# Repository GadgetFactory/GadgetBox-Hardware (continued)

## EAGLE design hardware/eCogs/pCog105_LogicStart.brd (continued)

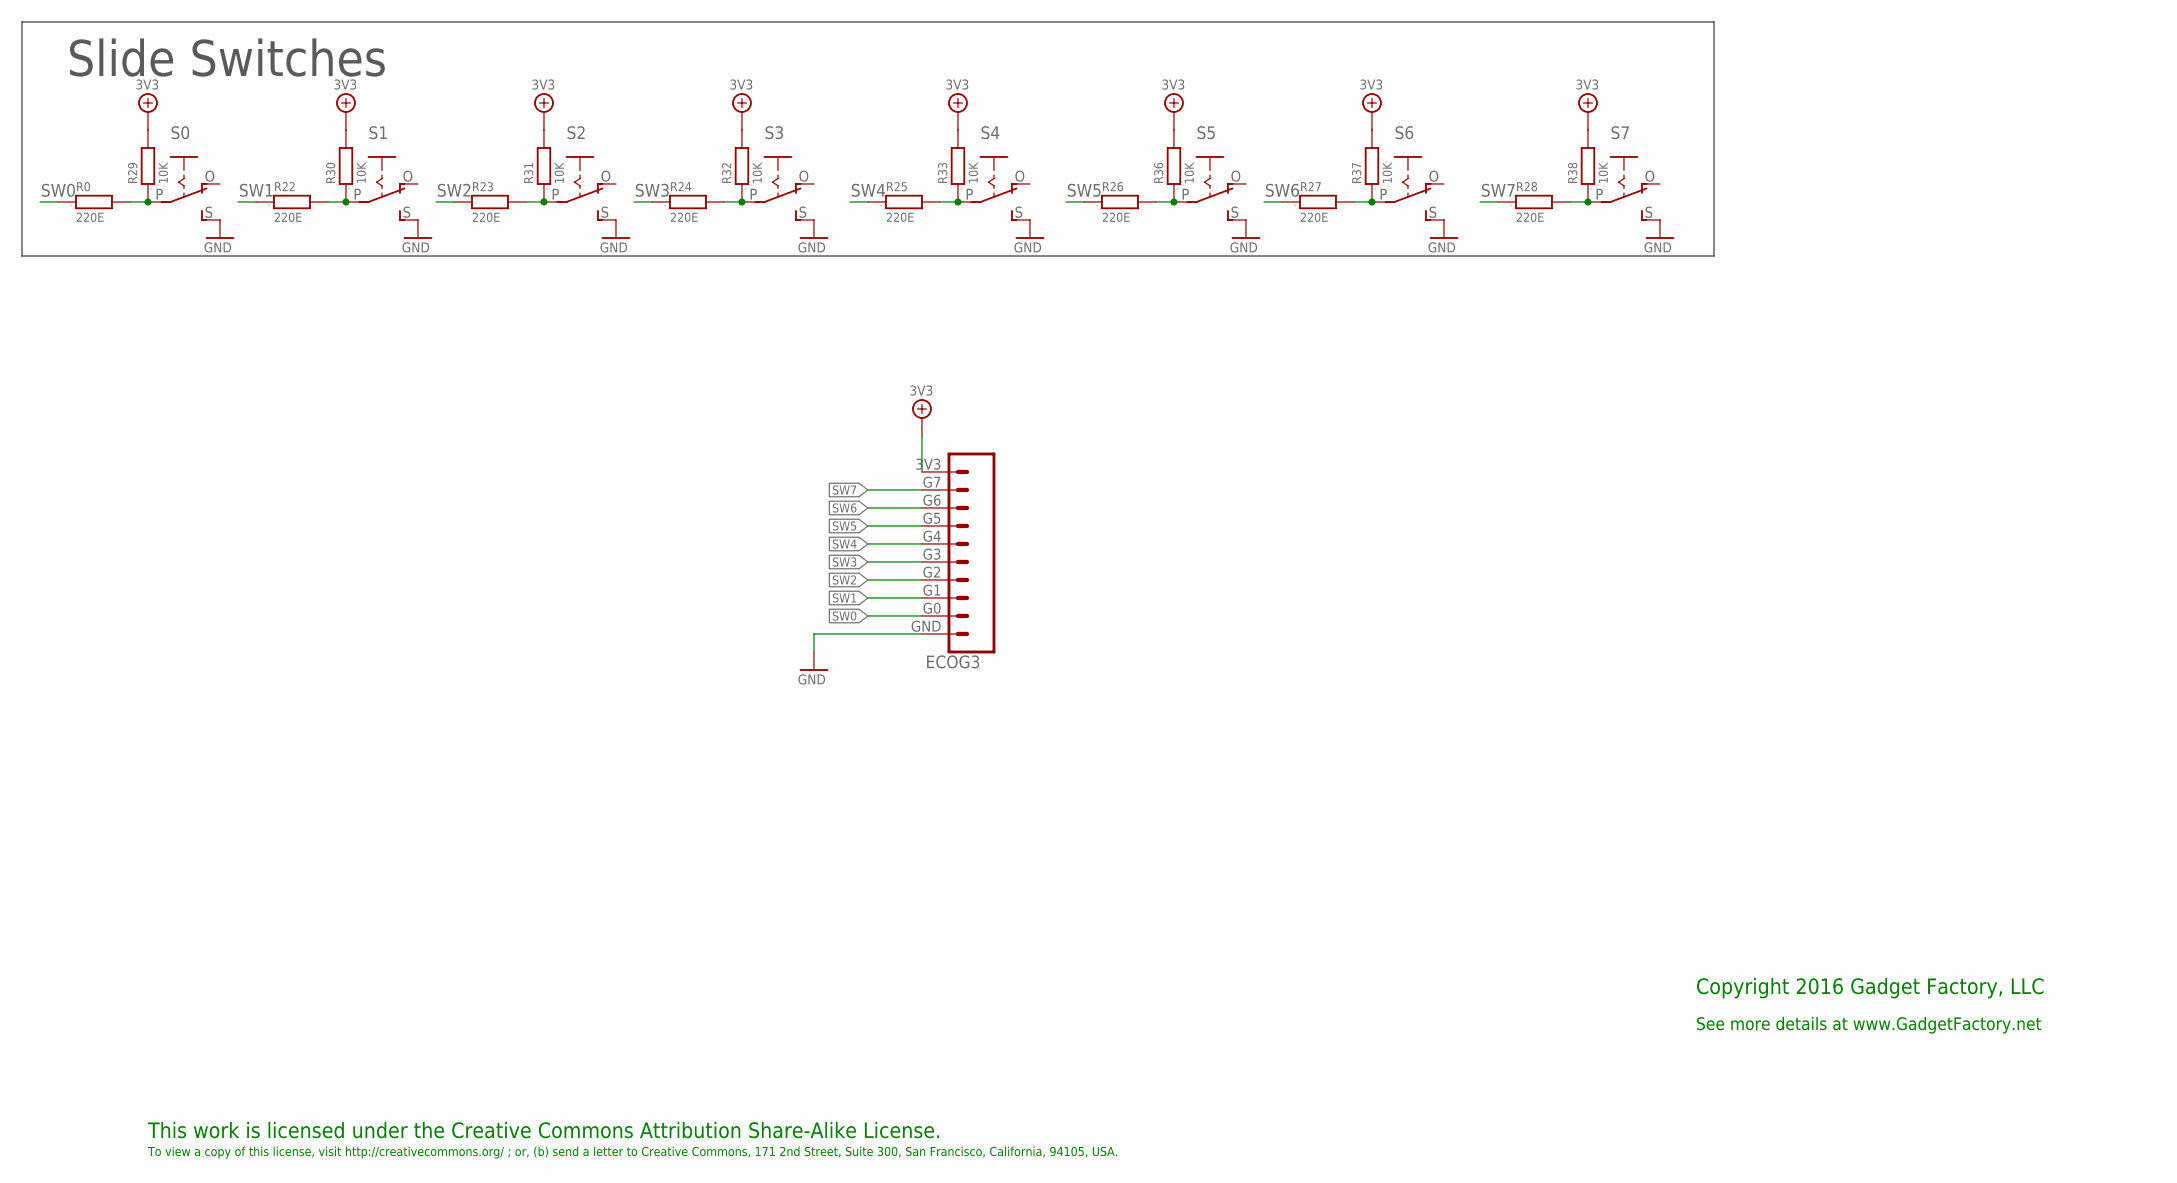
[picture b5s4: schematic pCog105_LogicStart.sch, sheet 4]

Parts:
ECOG3: ECOG_GENERAL_ROWTHROUGHOLE; ECOG_GENERAL_TH
R0, R22, R23, R24, R25, R26, R27, R28: 220E; 0603; PARTNO RMCF0603JT220R
R29, R30, R31, R32, R33, R36, R37, R38: 10K; 0603; PARTNO RMCF0603JT10K0
S0, S1, S2, S3, S4, S5, S6, S7: EG1218S; EG1218; PARTNO EG1218

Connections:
3V3: ECOG3.3V3, R29.2, R30.2, R31.2, R32.2, R33.2, R36.2, R37.2, R38.2; also elsewhere on the board
GND: ECOG3.GND, S0.S, S1.S, S2.S, S3.S, S4.S, S5.S, S6.S, S7.S; also elsewhere on the board
S5: R26.2, R36.1, S5.P
SW0: ECOG3.G0, R0.1
SW0_JOY_UP_IN: R0.2, R29.1, S0.P
SW1: ECOG3.G1, R22.1
SW1__JOY_DOWN_IN: R22.2, R30.1, S1.P
SW2: ECOG3.G2, R23.1
SW2_JOY_SELECT_IN: R23.2, R31.1, S2.P
SW3: ECOG3.G3, R24.1
SW3_JOY_RIGHT_IN: R24.2, R32.1, S3.P
SW4: ECOG3.G4, R25.1
SW4_JOY_LEFT_IN: R25.2, R33.1, S4.P
SW5: ECOG3.G5, R26.1
SW6: ECOG3.G6, R27.1
SW6_IN: R27.2, R37.1, S6.P
SW7: ECOG3.G7, R28.1
SW7_IN: R28.2, R38.1, S7.P

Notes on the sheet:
This work is licensed under the Creative Commons Attribution Share-Alike License.
To view a copy of this license, visit http://creativecommons.org/ ; or, (b) send a letter to Creative Commons, 171 2nd Street, Suite 300, San Francisco, California, 94105, USA.
Copyright 2016 Gadget Factory, LLC
See more details at www.GadgetFactory.net
Slide Switches

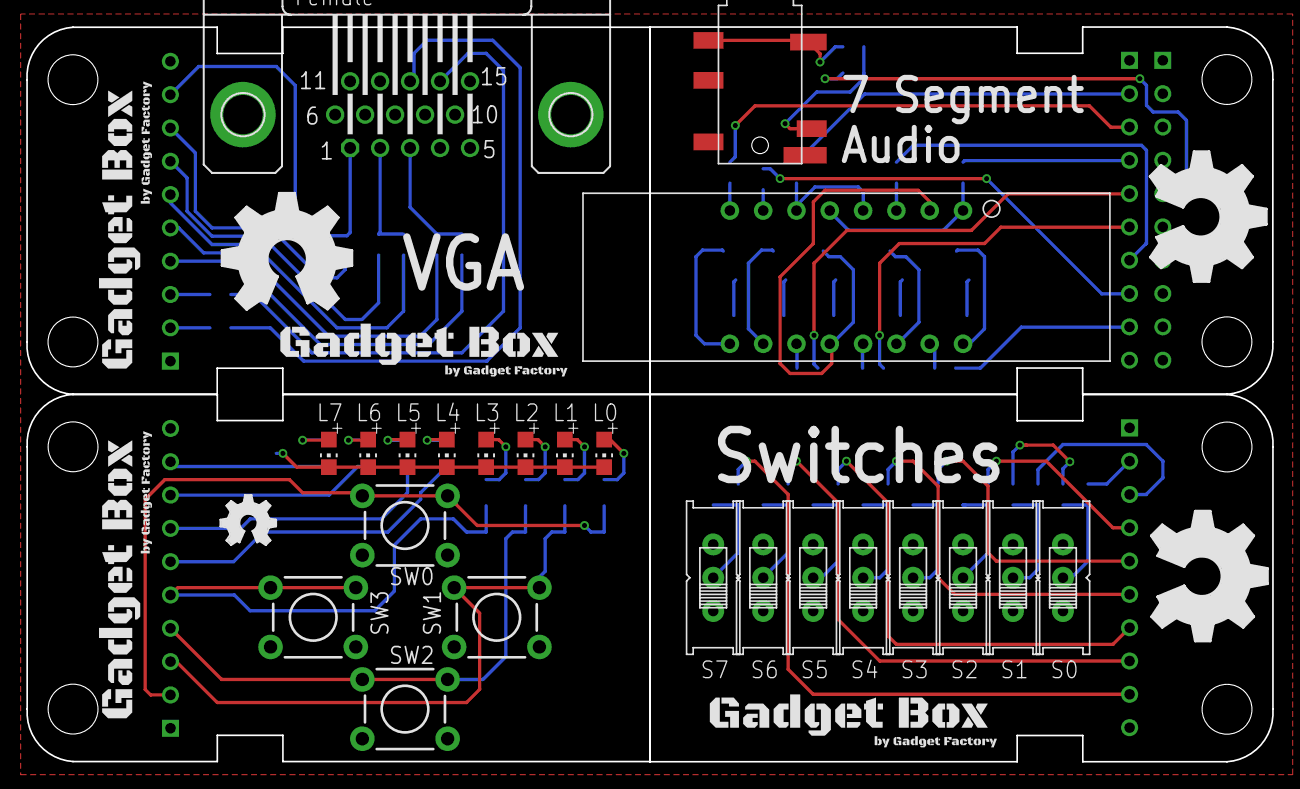
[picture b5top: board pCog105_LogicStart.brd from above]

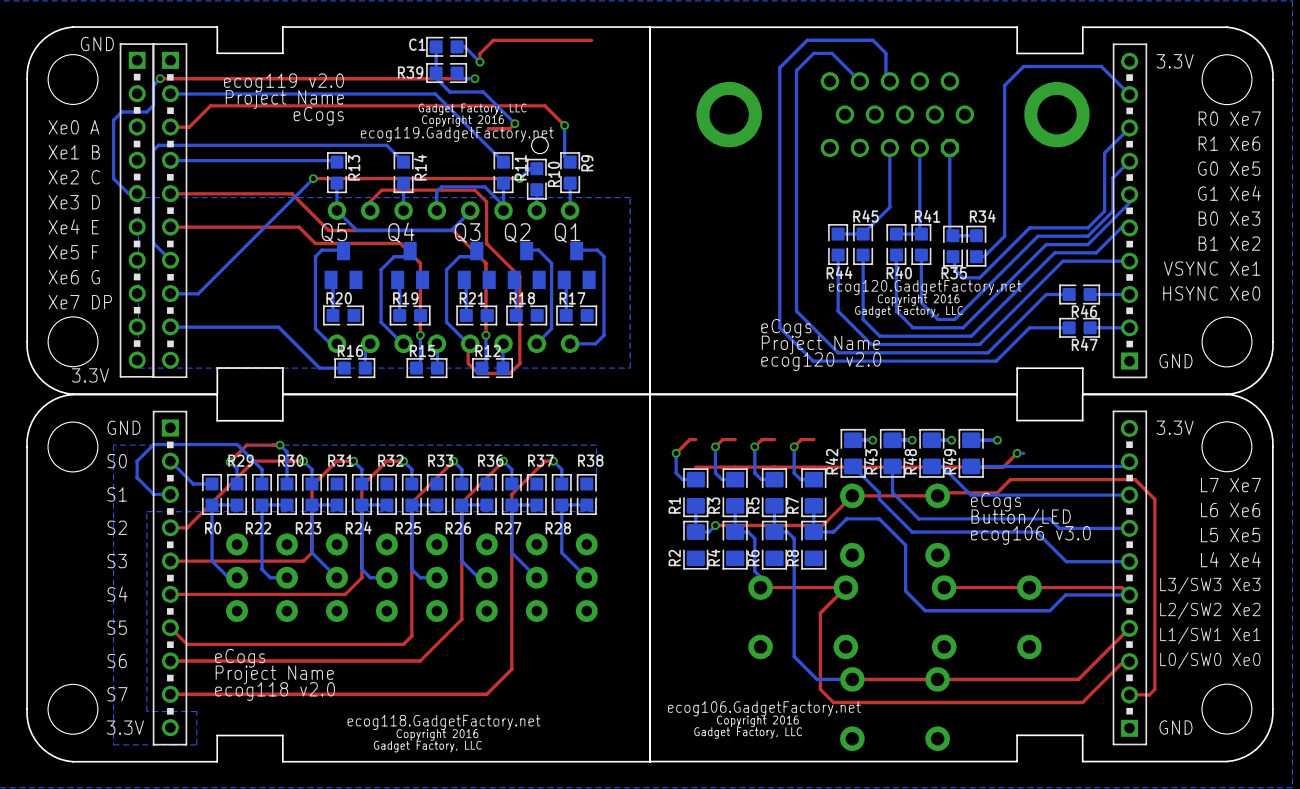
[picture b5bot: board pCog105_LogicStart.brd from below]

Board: 2 copper layers, 95.0 x 56.0 mm, 91 parts (56 on the bottom side), 75 nets.

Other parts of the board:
U$1, U$2, U$5, U$35: GADGETBOX_SMALL
U$6: OSHW_FILLX150_NOTEXT
U$10, U$18, U$28: OSHW_FILLX350_NOTEXT

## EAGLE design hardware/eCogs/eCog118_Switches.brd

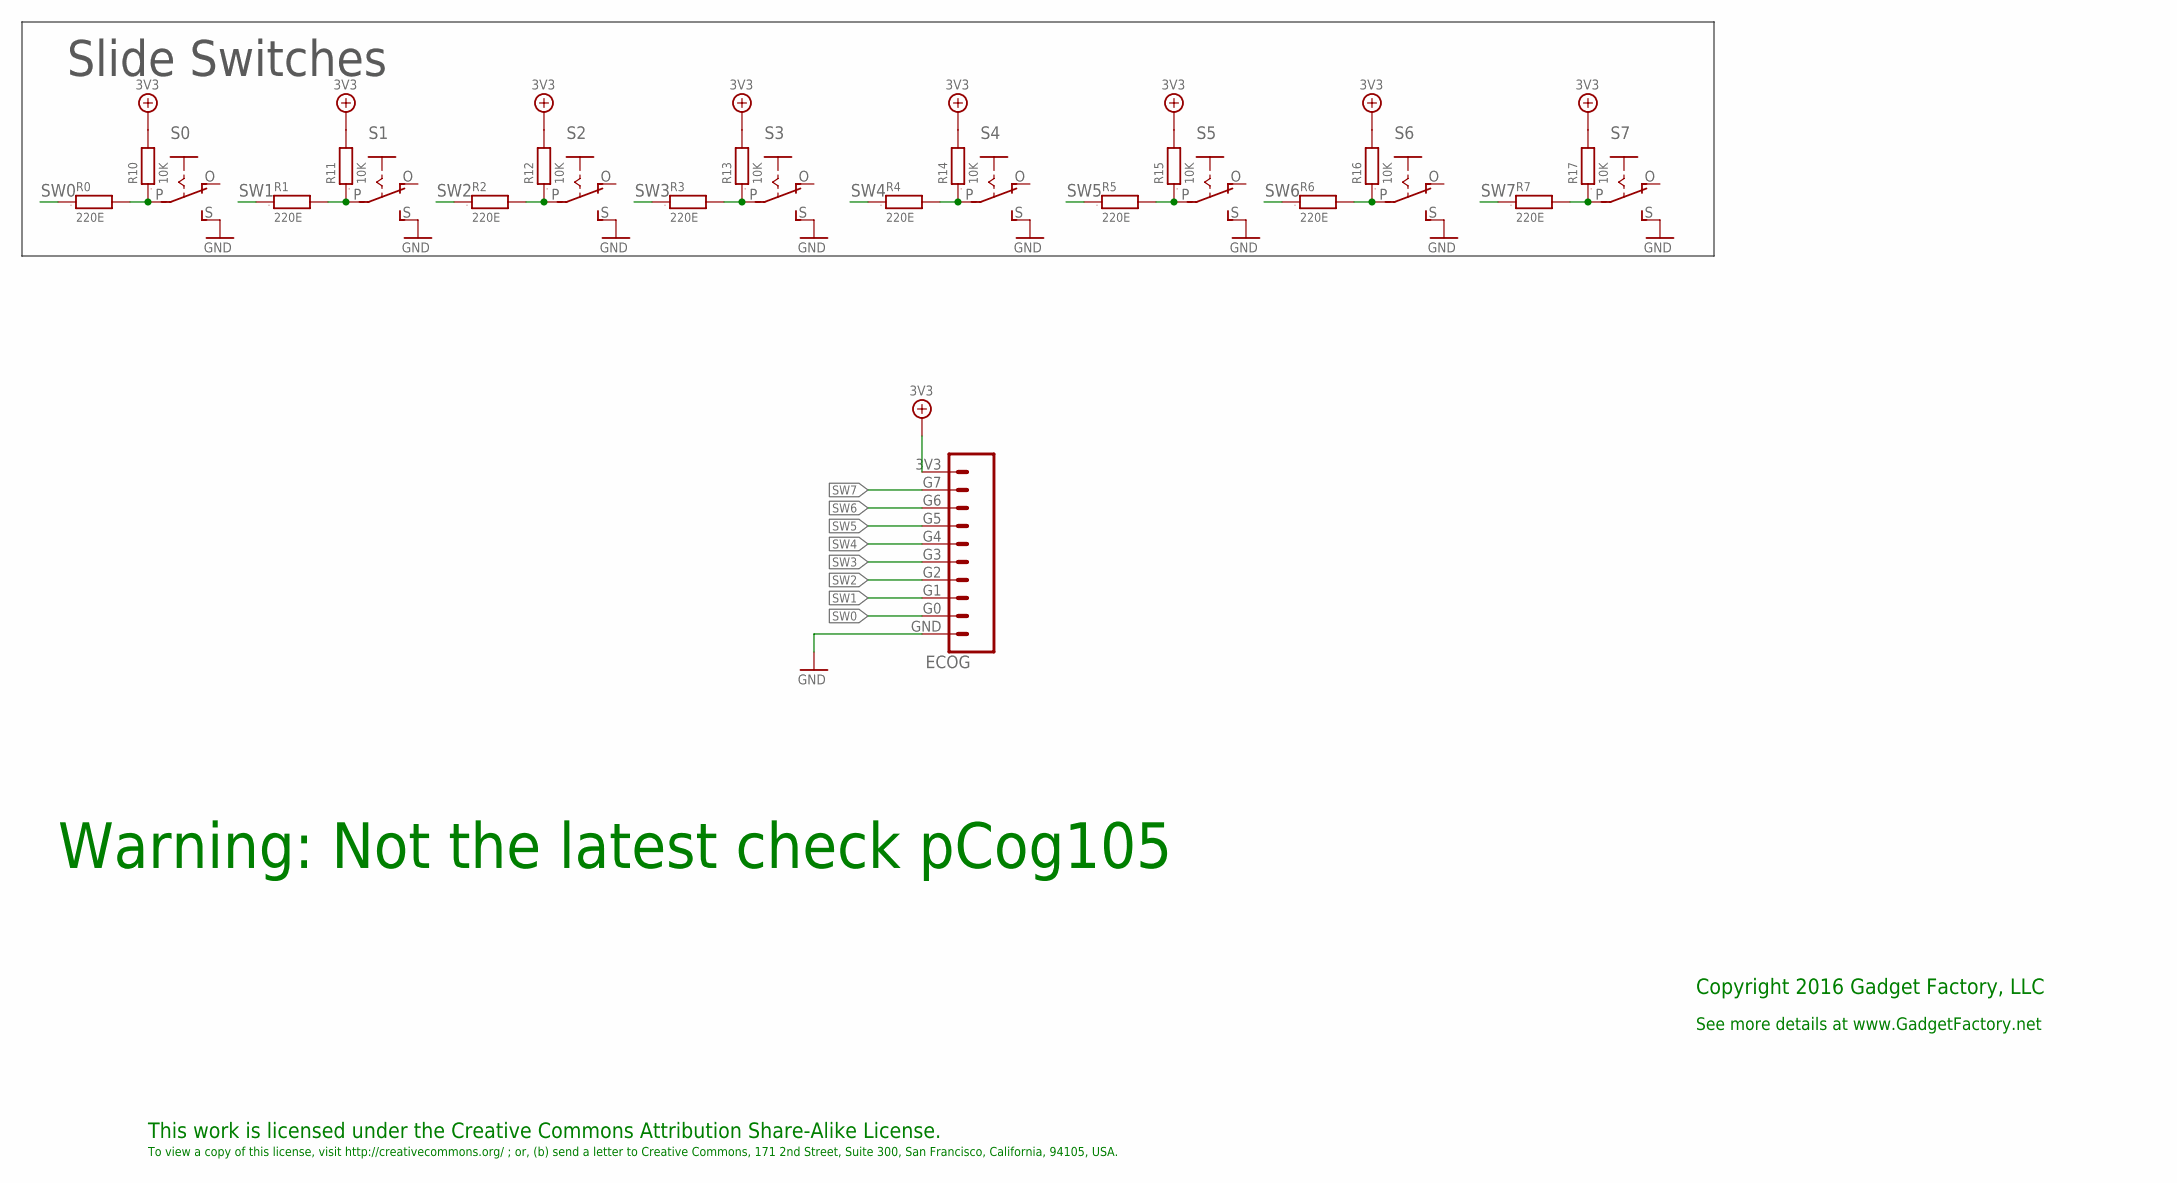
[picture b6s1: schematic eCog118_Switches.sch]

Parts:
ECOG: ECOG_GENERAL_ROWTHROUGHOLE; ECOG_GENERAL_TH
R0, R1, R2, R3, R4, R5, R6, R7: 220E; 0603; PARTNO RMCF0603JT220R
R10, R11, R12, R13, R14, R15, R16, R17: 10K; 0603; PARTNO RMCF0603JT10K0
S0, S1, S2, S3, S4, S5, S6, S7: EG1218S; EG1218; PARTNO EG1218

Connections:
3V3: ECOG.3V3, R10.2, R11.2, R12.2, R13.2, R14.2, R15.2, R16.2, R17.2
GND: ECOG.GND, S0.S, S1.S, S2.S, S3.S, S4.S, S5.S, S6.S, S7.S
S5: R5.2, R15.1, S5.P
SW0: ECOG.G0, R0.1
SW0_JOY_UP_IN: R0.2, R10.1, S0.P
SW1: ECOG.G1, R1.1
SW1__JOY_DOWN_IN: R1.2, R11.1, S1.P
SW2: ECOG.G2, R2.1
SW2_JOY_SELECT_IN: R2.2, R12.1, S2.P
SW3: ECOG.G3, R3.1
SW3_JOY_RIGHT_IN: R3.2, R13.1, S3.P
SW4: ECOG.G4, R4.1
SW4_JOY_LEFT_IN: R4.2, R14.1, S4.P
SW5: ECOG.G5, R5.1
SW6: ECOG.G6, R6.1
SW6_IN: R6.2, R16.1, S6.P
SW7: ECOG.G7, R7.1
SW7_IN: R7.2, R17.1, S7.P

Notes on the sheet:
This work is licensed under the Creative Commons Attribution Share-Alike License.
To view a copy of this license, visit http://creativecommons.org/ ; or, (b) send a letter to Creative Commons, 171 2nd Street, Suite 300, San Francisco, California, 94105, USA.
Copyright 2016 Gadget Factory, LLC
See more details at www.GadgetFactory.net
Slide Switches
Warning: Not the latest check pCog105

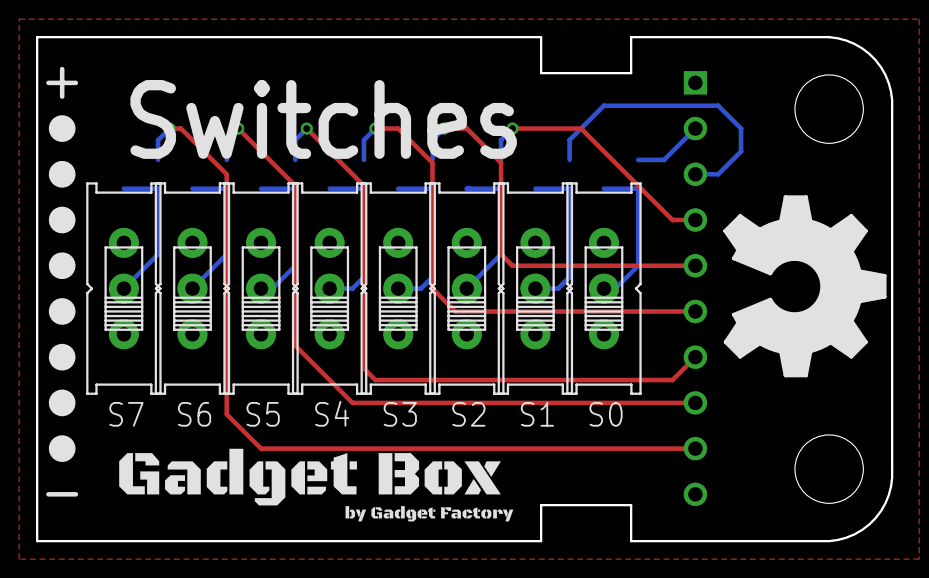
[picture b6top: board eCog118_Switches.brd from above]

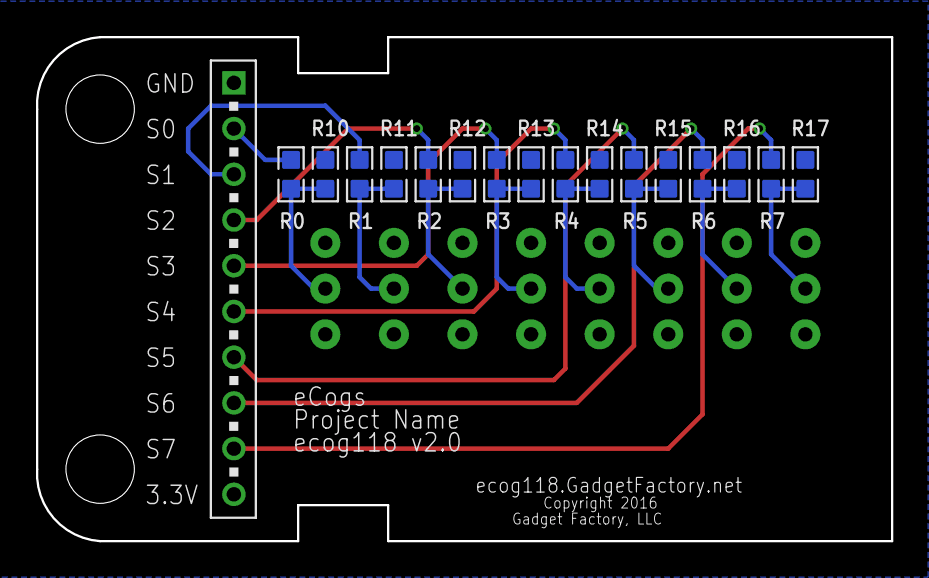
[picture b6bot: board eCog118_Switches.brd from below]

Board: 2 copper layers, 47.5 x 28.0 mm, 35 parts (16 on the bottom side), 18 nets.

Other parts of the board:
U$2, U$3, U$4, U$5, U$6, U$7, U$8, U$9: LEGEND_DIO
U$10: OSHW_FILLX350_NOTEXT
U$11: GADGETBOX_SMALL

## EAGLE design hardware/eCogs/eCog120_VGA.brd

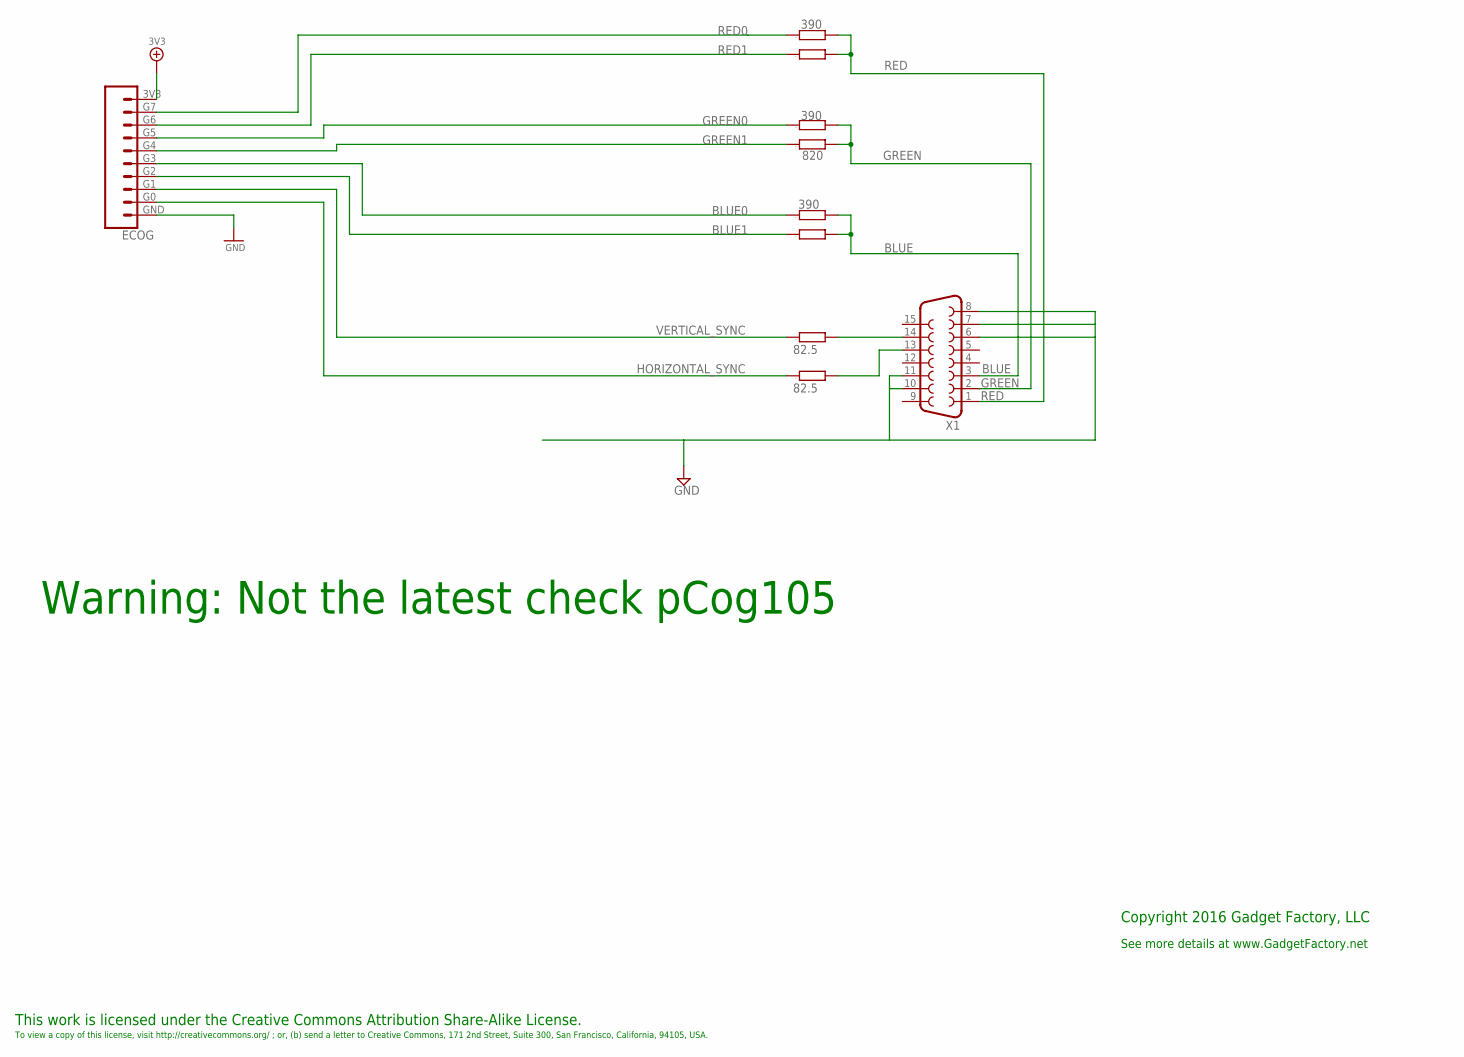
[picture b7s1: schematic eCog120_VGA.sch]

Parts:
ECOG: ECOG_GENERAL_ROWTHROUGHOLE; ECOG_GENERAL_TH
R34, R41, R45: 390; 0603; PARTNO RMCF0603JT3K90
R35, R40, R44: 820; 0603; PARTNO RMCF0603JT2K00
R46, R47: 82.5; 0603; PARTNO RMCF0603FT82R5
X1: F15HDH; HDF15H; PARTNO 1-1734530-1

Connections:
3V3: ECOG.3V3
BLUE: R44.2, R45.2, X1.3
BLUE0: ECOG.G3, R45.1
BLUE1: ECOG.G2, R44.1
GND: ECOG.GND, X1.6, X1.7, X1.8, X1.10, X1.11
GREEN: R40.2, R41.2, X1.2
GREEN0: ECOG.G5, R41.1
GREEN1: ECOG.G4, R40.1
HORIZONTAL_SYNC: ECOG.G0, R47.1
unnamed: R47.2, X1.13
unnamed: R46.2, X1.14
RED: R34.2, R35.2, X1.1
RED0: ECOG.G7, R34.1
RED1: ECOG.G6, R35.1
VERTICAL_SYNC: ECOG.G1, R46.1

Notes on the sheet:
This work is licensed under the Creative Commons Attribution Share-Alike License.
To view a copy of this license, visit http://creativecommons.org/ ; or, (b) send a letter to Creative Commons, 171 2nd Street, Suite 300, San Francisco, California, 94105, USA.
Copyright 2016 Gadget Factory, LLC
See more details at www.GadgetFactory.net
Warning: Not the latest check pCog105

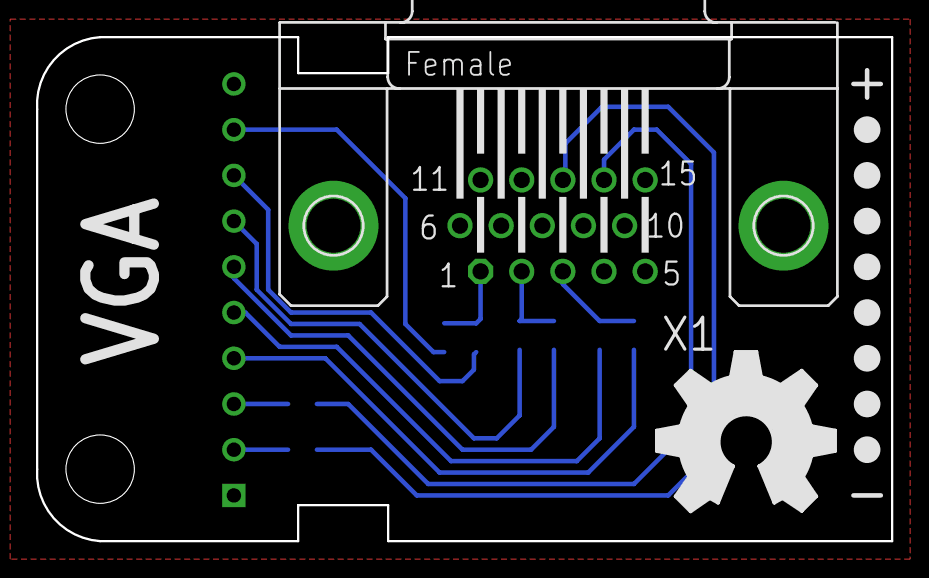
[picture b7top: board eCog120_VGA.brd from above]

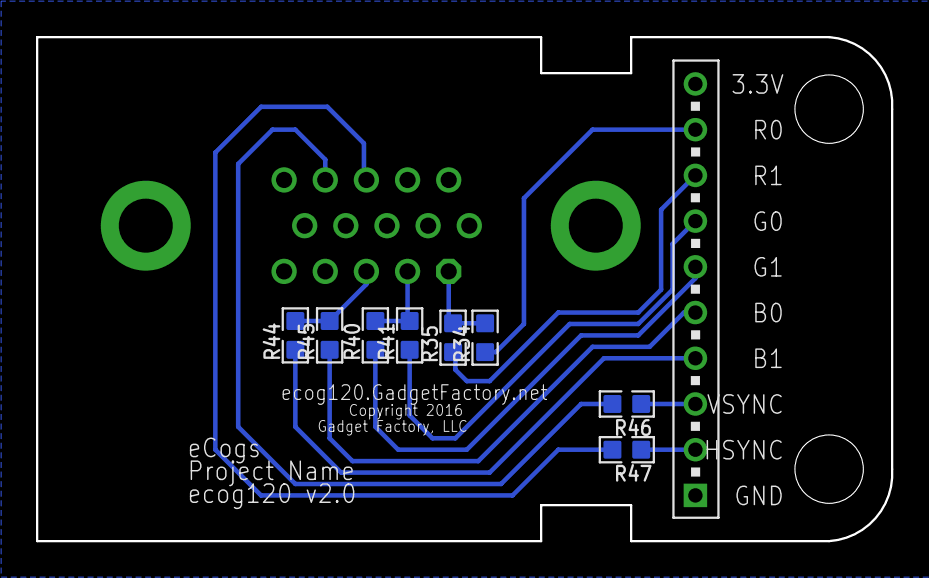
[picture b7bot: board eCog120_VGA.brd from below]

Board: 2 copper layers, 47.5 x 28.0 mm, 19 parts (8 on the bottom side), 14 nets.

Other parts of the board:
U$1, U$2, U$3, U$4, U$5, U$6, U$7, U$8: LEGEND_DIO
U$10: OSHW_FILLX350_NOTEXT

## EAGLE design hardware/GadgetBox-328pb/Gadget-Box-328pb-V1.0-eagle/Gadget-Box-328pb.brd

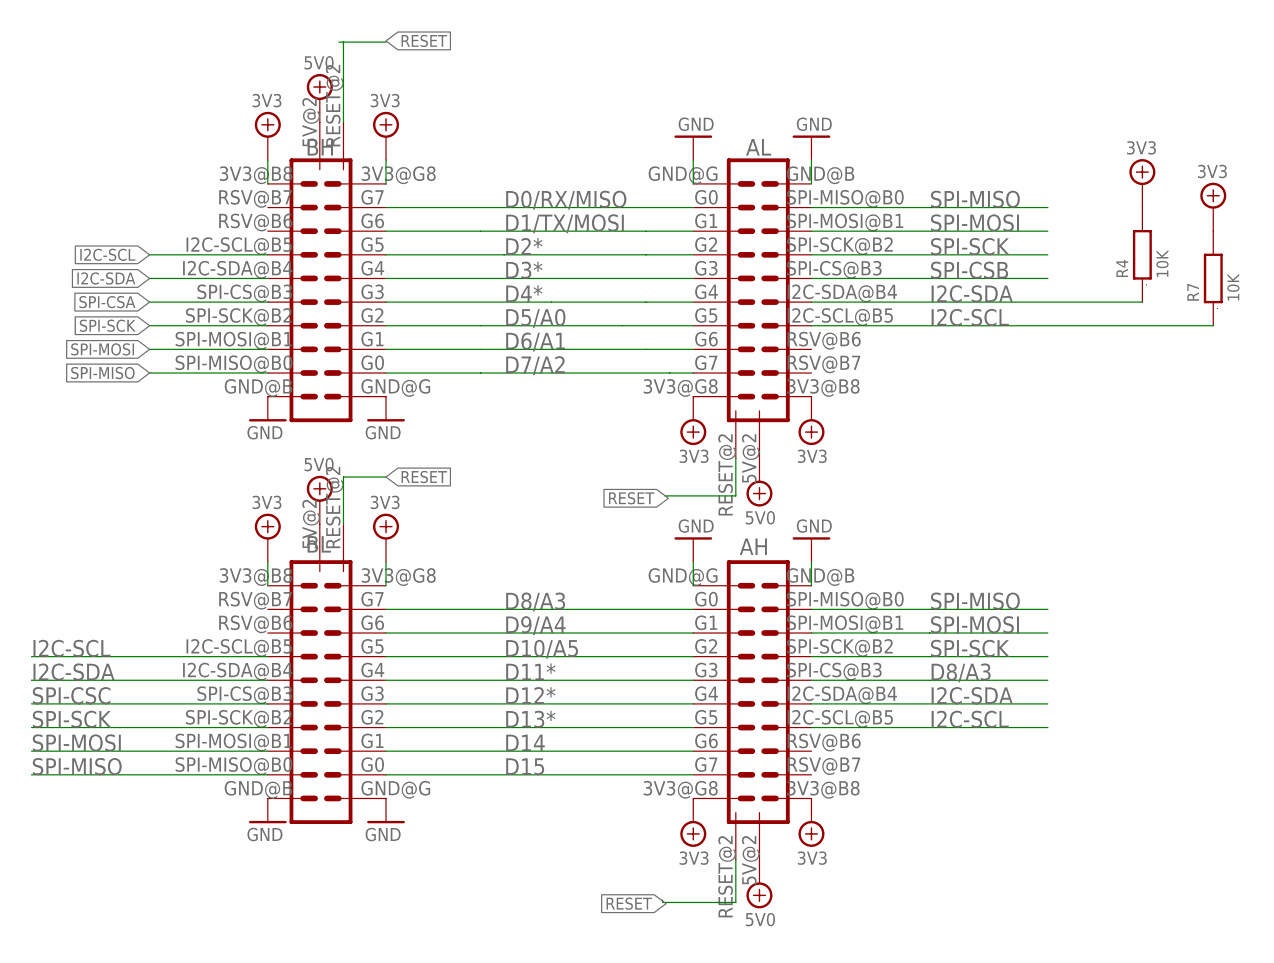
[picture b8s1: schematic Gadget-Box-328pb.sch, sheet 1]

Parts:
AH: ECOGECOG_SLOT_ALT1; ECOG_ALT1; PARTNO PPPC102LFBN-RC,SULLINS CONNECTOR SOLUTI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
AL: ECOGECOG_SLOT_ALT1; ECOG_ALT1; PARTNO PPPC102LFBN-RC,SULLINS CONNECTOR SOLUTI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
BH: ECOGECOG_SLOT_ALT1; ECOG_ALT1; PARTNO PPPC102LFBN-RC,SULLINS CONNECTOR SOLUTI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
BL: ECOGECOG_SLOT_ALT1; ECOG_ALT1; PARTNO PPPC102LFBN-RC,SULLINS CONNECTOR SOLUTI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
R4, R7: 10K; 0603; PARTNO RC0603JR-0710KL,YAGEO (VA),dk,311-10KGR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

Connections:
3V3: AH.3V3@B8 (3V3), AH.3V3@G8 (3V3), AL.3V3@B8 (3V3), AL.3V3@G8 (3V3), BH.3V3@B8 (3V3), BH.3V3@G8 (3V3), BL.3V3@B8 (3V3), BL.3V3@G8 (3V3), R4.2, R7.2; also elsewhere on the board
5V0: AH.5V@2 (5V), AL.5V@2 (5V), BH.5V@2 (5V), BL.5V@2 (5V); also elsewhere on the board
D0/RX/MISO: AL.G0, BH.G7; also elsewhere on the board
D1/TX/MOSI: AL.G1, BH.G6; also elsewhere on the board
D2*: AL.G2, BH.G5; also elsewhere on the board
D3*: AL.G3, BH.G4; also elsewhere on the board
D4*: AL.G4, BH.G3; also elsewhere on the board
D5/A0: AL.G5, BH.G2; also elsewhere on the board
D6/A1: AL.G6, BH.G1; also elsewhere on the board
D7/A2: AL.G7, BH.G0; also elsewhere on the board
D8/A3: AH.G0, AH.SPI-CS@B3 (SPI-CS), BL.G7; also elsewhere on the board
D9/A4: AH.G1, BL.G6; also elsewhere on the board
D10/A5: AH.G2, BL.G5; also elsewhere on the board
D11*: AH.G3, BL.G4; also elsewhere on the board
D12*: AH.G4, BL.G3; also elsewhere on the board
D13*: AH.G5, BL.G2; also elsewhere on the board
D14: AH.G6, BL.G1; also elsewhere on the board
D15: AH.G7, BL.G0; also elsewhere on the board
GND: AH.GND@B (GND), AH.GND@G (GND), AL.GND@B (GND), AL.GND@G (GND), BH.GND@B (GND), BH.GND@G (GND), BL.GND@B (GND), BL.GND@G (GND); also elsewhere on the board
I2C-SCL: AH.I2C-SCL@B5 (I2C-SCL), AL.I2C-SCL@B5 (I2C-SCL), BH.I2C-SCL@B5 (I2C-SCL), BL.I2C-SCL@B5 (I2C-SCL), R7.1; also elsewhere on the board
I2C-SDA: AH.I2C-SDA@B4 (I2C-SDA), AL.I2C-SDA@B4 (I2C-SDA), BH.I2C-SDA@B4 (I2C-SDA), BL.I2C-SDA@B4 (I2C-SDA), R4.1; also elsewhere on the board
RESET: AH.RESET@2 (RESET), AL.RESET@2 (RESET), BH.RESET@2 (RESET), BL.RESET@2 (RESET); also elsewhere on the board
SPI-CSA: BH.SPI-CS@B3 (SPI-CS); also elsewhere on the board
SPI-CSB: AL.SPI-CS@B3 (SPI-CS); also elsewhere on the board
SPI-CSC: BL.SPI-CS@B3 (SPI-CS); also elsewhere on the board
SPI-MISO: AH.SPI-MISO@B0 (SPI-MISO), AL.SPI-MISO@B0 (SPI-MISO), BH.SPI-MISO@B0 (SPI-MISO), BL.SPI-MISO@B0 (SPI-MISO); also elsewhere on the board
SPI-MOSI: AH.SPI-MOSI@B1 (SPI-MOSI), AL.SPI-MOSI@B1 (SPI-MOSI), BH.SPI-MOSI@B1 (SPI-MOSI), BL.SPI-MOSI@B1 (SPI-MOSI); also elsewhere on the board
SPI-SCK: AH.SPI-SCK@B2 (SPI-SCK), AL.SPI-SCK@B2 (SPI-SCK), BH.SPI-SCK@B2 (SPI-SCK), BL.SPI-SCK@B2 (SPI-SCK); also elsewhere on the board

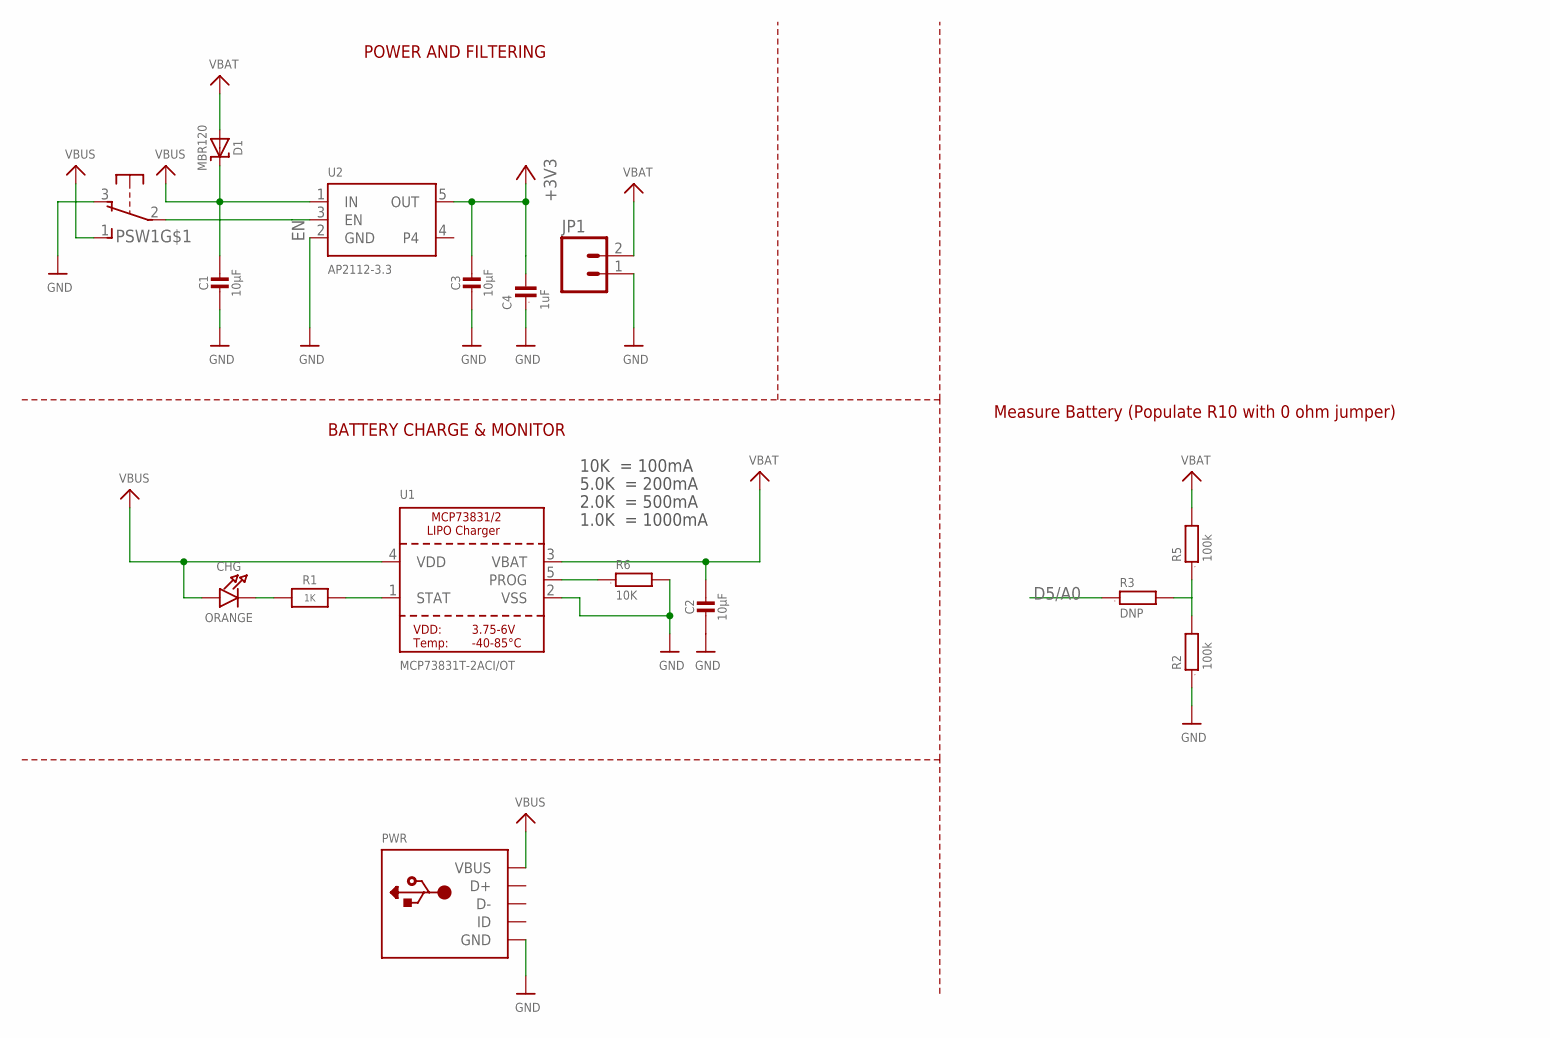
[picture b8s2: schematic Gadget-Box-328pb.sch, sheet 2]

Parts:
C1, C2, C3: 10µF; 0805-NO; PARTNO CL21F106ZPFNNNE,Samsung,DK,1276-3012-1-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
C4: 1uF; 0603; PARTNO C1608X5R1A105K080AC,TDK CORPORATION (VA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
CHG: ORANGE; CHIPLED_0805_NOOUTLINE; PARTNO LTST-C171EKT,LITE-ON INC (VA),DK,160-14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
D1: MBR120; SOD-123; PARTNO MBR120VLSFT3G,on semiconductor,dk,MBR12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
JP1: M02-JST-2-PTH-NO_SILK; JST-2-PTH-NS; PARTNO B2B-PH-SM4-TB(LF)(SN),JST SALES AMERICA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
PSW1: OS102011MA1Q; PARTNO OS102011MA1QN1,C&K Components,dk,CKN955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
PWR: USBMINIB; USB-MINIB; PARTNO USB-M26FTR,On Shore Technology Inc,DK,E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
R1: 1K; 0603-NO; PARTNO RC0603JR-071KL,YAGEO (VA),dk,311-1.0KGR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
R2, R5: 100k; 0603; PARTNO RC0603JR-07100KL,YAGEO (VA),dk,311-100K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
R3: DNP; 0603
R6: 10K; 0603; PARTNO RC0603JR-0710KL,YAGEO (VA),dk,311-10KGR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
U1: MCP73831T-2ACI/OT; SOT23-5; PARTNO MCP73831T-2ACI/OT,MICROCHIP TECHNOLOGY 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
U2: AP2112-3.3; SOT23-5; PARTNO AP2112K-3.3TRG1,Diodes Incorporated,dk,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

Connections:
3V3: C3.1, C4.2, U2.5 (OUT); also elsewhere on the board
5V0: C1.1, CHG.A, D1.C, PSW1.1 (S), PWR.VBUS, U1.4 (VDD), U2.1 (IN); also elsewhere on the board
D5/A0: R3.1; also elsewhere on the board
EN: PSW1.2, U2.3 (EN)
GND: C1.2, C2.2, C3.2, C4.1, JP1.1, PSW1.3 (O), PWR.GND, R2.1, R6.2, U1.2 (VSS), U2.2 (GND); also elsewhere on the board
unnamed: CHG.C, R1.1
unnamed: R2.2, R3.2, R5.1
unnamed: R1.2, U1.1 (STAT)
unnamed: R6.1, U1.5 (PROG)
VBAT: C2.1, D1.A, JP1.2, R5.2, U1.3 (VBAT)

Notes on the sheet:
POWER AND FILTERING
10K = 100mA
5.0K = 200mA
2.0K = 500mA
1.0K = 1000mA
BATTERY CHARGE & MONITOR
Measure Battery (Populate R10 with 0 ohm jumper)

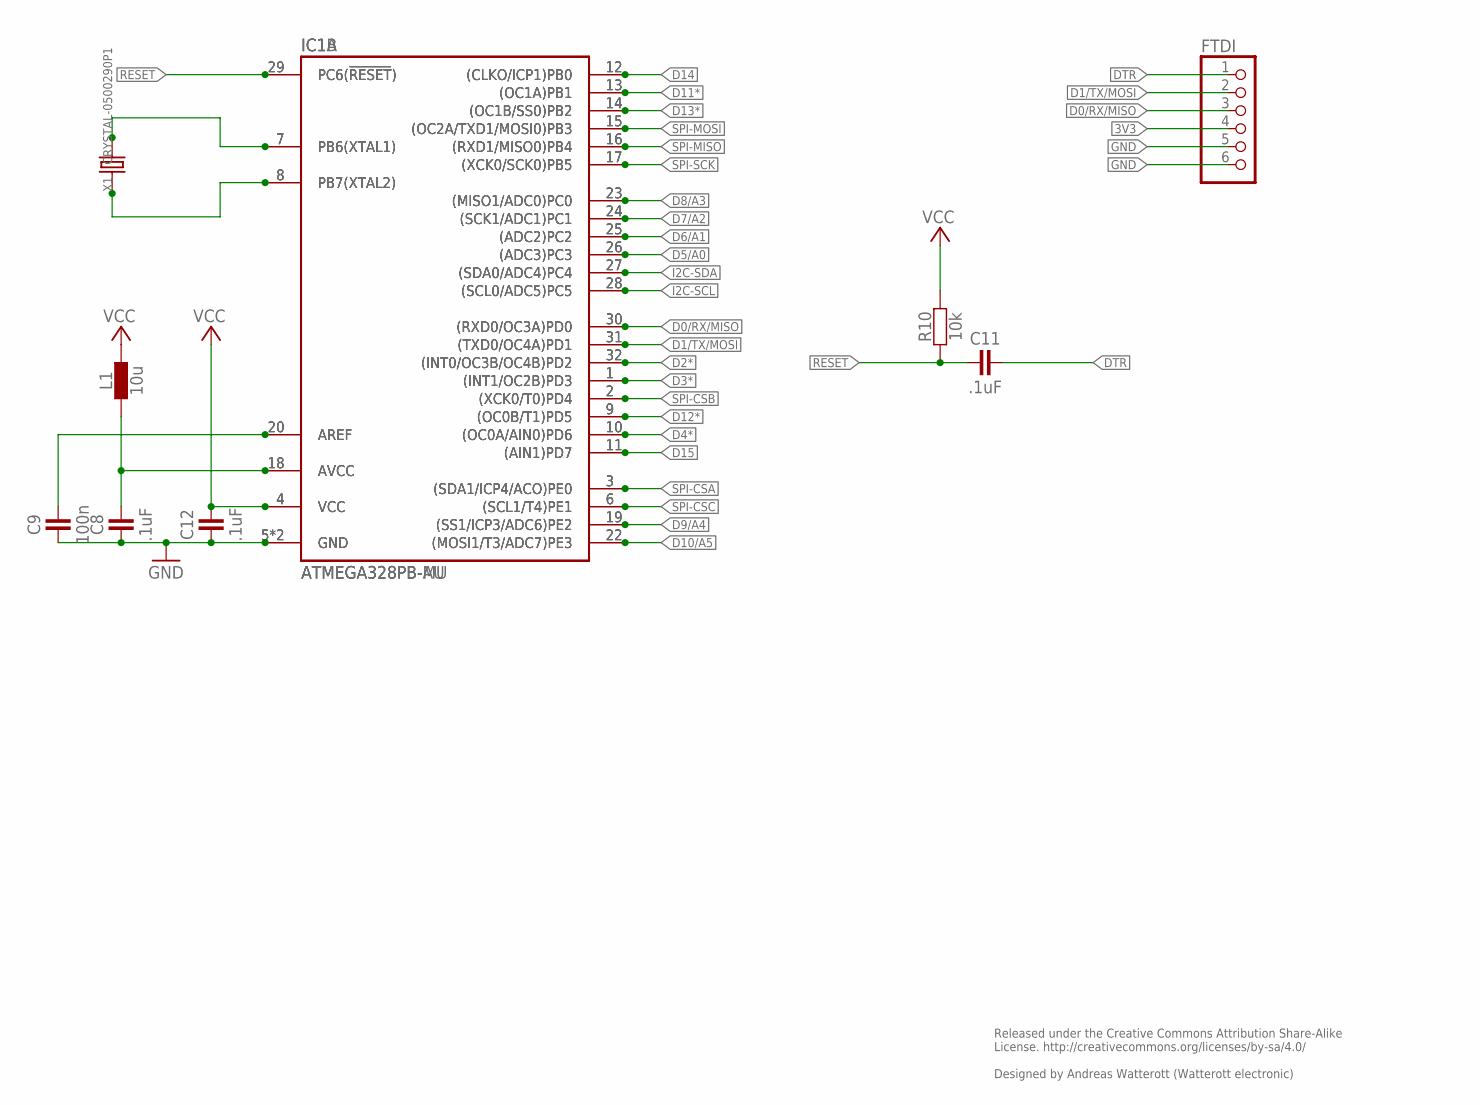
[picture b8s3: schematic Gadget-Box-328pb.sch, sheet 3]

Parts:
C8, C12: .1uF; C0805
C9: 100n; C0805
C11: .1uF; C0603
FTDI: PINHD-1X6; 1X06
IC1A: ATMEGA328PB-AU; TQFP32
IC1B: ATMEGA328PB-MU; QFN32-PAD
L1: 10u; C0603
R10: 10k; C0603
X1: CRYSTAL-0500290P1; 2P-SMD-5.0X3.2

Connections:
3V3: C12.2, FTDI.4, IC1A.4 (VCC), IC1B.4 (VCC), L1.2, R10.2; also elsewhere on the board
AREF: C9.2, IC1A.20 (AREF), IC1B.20 (AREF)
AVCC: C8.2, IC1A.18 (AVCC), IC1B.18 (AVCC), L1.1
D0/RX/MISO: FTDI.3, IC1A.30 ((RXD0/OC3A)PD0), IC1B.30 ((RXD0/OC3A)PD0); also elsewhere on the board
D1/TX/MOSI: FTDI.2, IC1A.31 ((TXD0/OC4A)PD1), IC1B.31 ((TXD0/OC4A)PD1); also elsewhere on the board
D2*: IC1A.32 ((INT0/OC3B/OC4B)PD2), IC1B.32 ((INT0/OC3B/OC4B)PD2); also elsewhere on the board
D3*: IC1A.1 ((INT1/OC2B)PD3), IC1B.1 ((INT1/OC2B)PD3); also elsewhere on the board
D4*: IC1A.10 ((OC0A/AIN0)PD6), IC1B.10 ((OC0A/AIN0)PD6); also elsewhere on the board
D5/A0: IC1A.26 ((ADC3)PC3), IC1B.26 ((ADC3)PC3); also elsewhere on the board
D6/A1: IC1A.25 ((ADC2)PC2), IC1B.25 ((ADC2)PC2); also elsewhere on the board
D7/A2: IC1A.24 ((SCK1/ADC1)PC1), IC1B.24 ((SCK1/ADC1)PC1); also elsewhere on the board
D8/A3: IC1A.23 ((MISO1/ADC0)PC0), IC1B.23 ((MISO1/ADC0)PC0); also elsewhere on the board
D9/A4: IC1A.19 ((SS1/ICP3/ADC6)PE2), IC1B.19 ((SS1/ICP3/ADC6)PE2); also elsewhere on the board
D10/A5: IC1A.22 ((MOSI1/T3/ADC7)PE3), IC1B.22 ((MOSI1/T3/ADC7)PE3); also elsewhere on the board
D11*: IC1A.13 ((OC1A)PB1), IC1B.13 ((OC1A)PB1); also elsewhere on the board
D12*: IC1A.9 ((OC0B/T1)PD5), IC1B.9 ((OC0B/T1)PD5); also elsewhere on the board
D13*: IC1A.14 ((OC1B/SS0)PB2), IC1B.14 ((OC1B/SS0)PB2); also elsewhere on the board
D14: IC1A.12 ((CLKO/ICP1)PB0), IC1B.12 ((CLKO/ICP1)PB0); also elsewhere on the board
D15: IC1A.11 ((AIN1)PD7), IC1B.11 ((AIN1)PD7); also elsewhere on the board
DTR: C11.2, FTDI.1
GND: C8.1, C9.1, C12.1, FTDI.5, FTDI.6, IC1A.5 (GND), IC1A.21 (GND), IC1B.5 (GND), IC1B.21 (GND); also elsewhere on the board
I2C-SCL: IC1A.28 ((SCL0/ADC5)PC5), IC1B.28 ((SCL0/ADC5)PC5); also elsewhere on the board
I2C-SDA: IC1A.27 ((SDA0/ADC4)PC4), IC1B.27 ((SDA0/ADC4)PC4); also elsewhere on the board
unnamed: IC1A.8 (PB7(XTAL2)), IC1B.8 (PB7(XTAL2)), X1.1
unnamed: IC1A.7 (PB6(XTAL1)), IC1B.7 (PB6(XTAL1)), X1.2
RESET: C11.1, IC1A.29 (PC6(!RESET!)), IC1B.29 (PC6(!RESET!)), R10.1; also elsewhere on the board
SPI-CSA: IC1A.3 ((SDA1/ICP4/ACO)PE0), IC1B.3 ((SDA1/ICP4/ACO)PE0); also elsewhere on the board
SPI-CSB: IC1A.2 ((XCK0/T0)PD4), IC1B.2 ((XCK0/T0)PD4); also elsewhere on the board
SPI-CSC: IC1A.6 ((SCL1/T4)PE1), IC1B.6 ((SCL1/T4)PE1); also elsewhere on the board
SPI-MISO: IC1A.16 ((RXD1/MISO0)PB4), IC1B.16 ((RXD1/MISO0)PB4); also elsewhere on the board
SPI-MOSI: IC1A.15 ((OC2A/TXD1/MOSI0)PB3), IC1B.15 ((OC2A/TXD1/MOSI0)PB3); also elsewhere on the board
SPI-SCK: IC1A.17 ((XCK0/SCK0)PB5), IC1B.17 ((XCK0/SCK0)PB5); also elsewhere on the board

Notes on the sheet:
Released under the Creative Commons Attribution Share-Alike License. http://creativecommons.org/licenses/by-sa/4.0/ Designed by Andreas Watterott (Watterott electronic)
